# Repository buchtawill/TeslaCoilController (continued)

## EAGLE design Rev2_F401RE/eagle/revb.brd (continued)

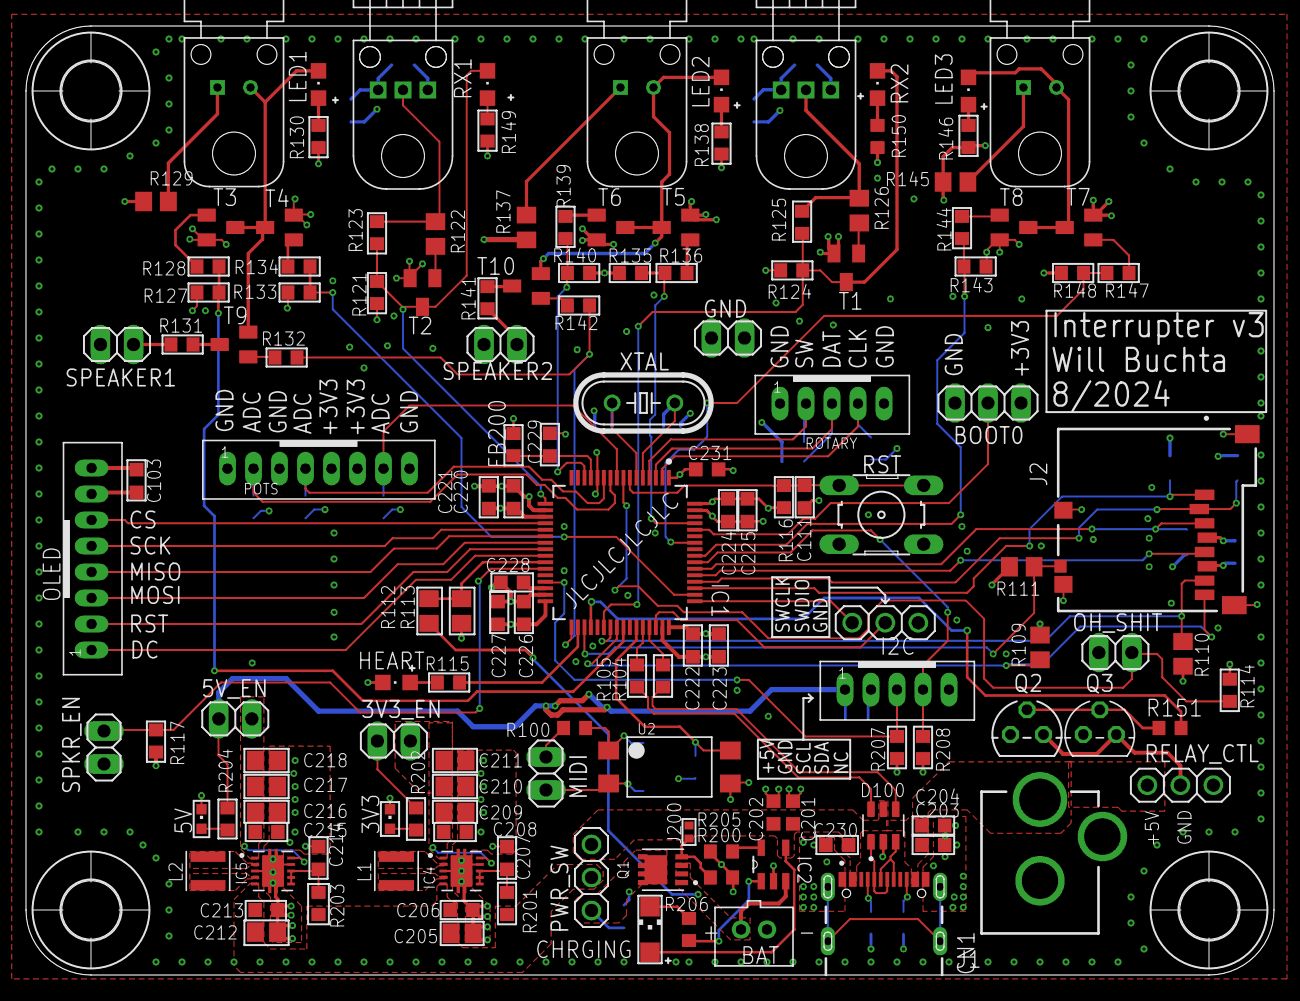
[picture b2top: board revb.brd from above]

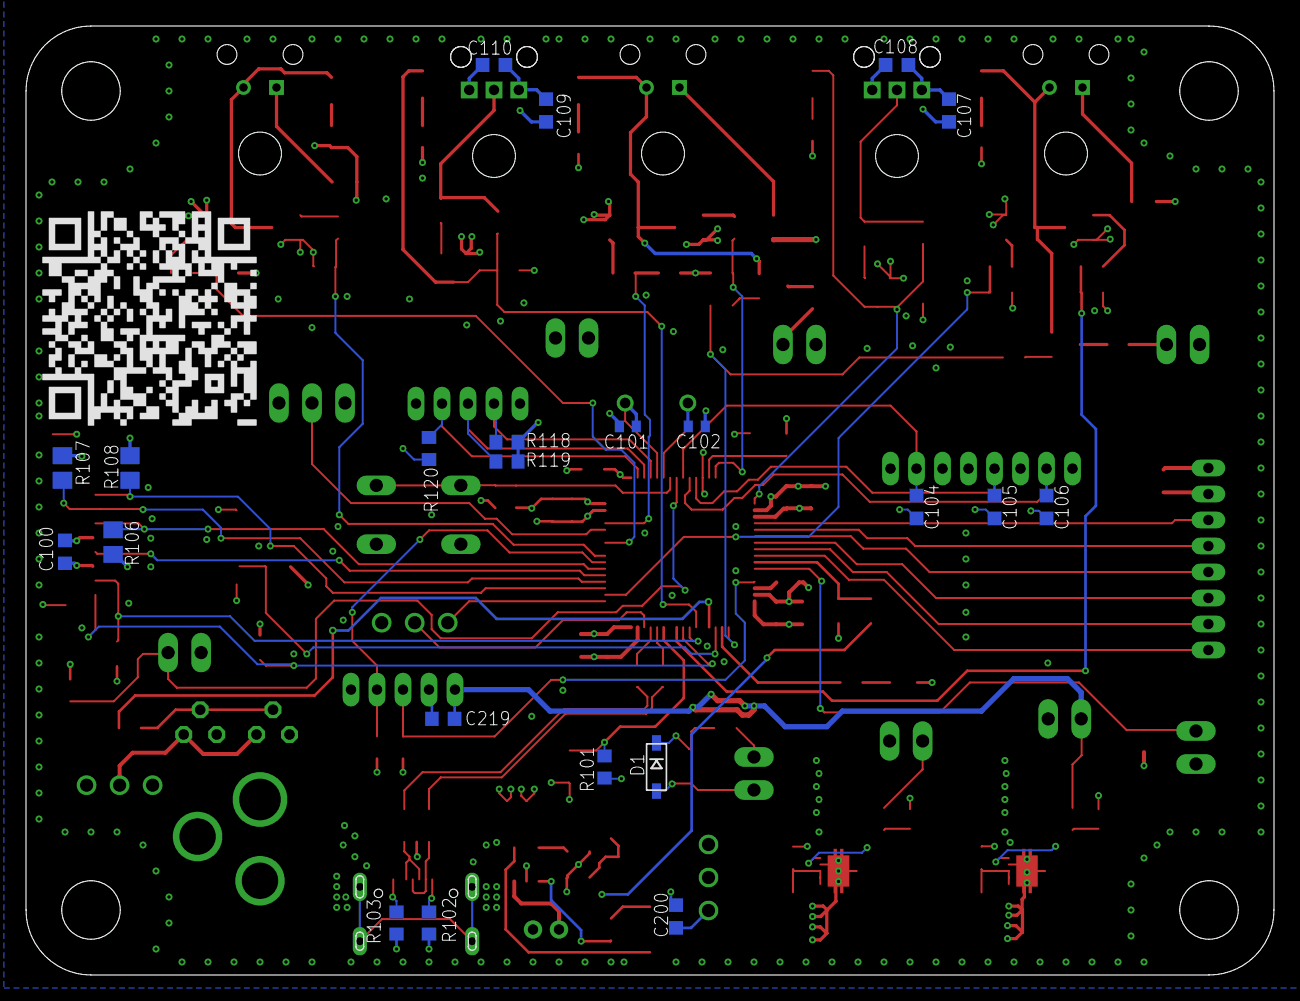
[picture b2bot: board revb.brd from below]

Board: 4 copper layers, 96.0 x 73.0 mm, 169 parts (22 on the bottom side), 107 nets.

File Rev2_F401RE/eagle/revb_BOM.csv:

Qty,Value,Device,Package,Parts,Description,Column1,_1
1,,10-XX,B3F-10XX,RST,OMRON SWITCH,,
1,,CRYSTALHC49S,HC49/S,XTAL,CRYSTAL,,
1,,JST_2PIN-THM,JST-PH-2-THM,BAT,JST 2-Pin Connectors of various flavors,,
2,,LEDCHIPLED_0603,CHIPLED_0603,"3V3, 5V",LED,,
6,,LEDCHIPLED_0805,CHIPLED_0805,"HEART, LED1, LED2, LED3, RX1, RX2",LED,,
1,,LEDCHIPLED_1206,CHIPLED_1206,CHRGING,LED,,
6,,PINHD-1X2,1X02,"GND, MIDI, OH_SHIT, SPEAKER1, SPEAKER2, SPKR_EN",PIN HEADER,,
3,,PINHD-1X3,1X03,"BOOT0, PWR_SW, SWD",PIN HEADER,,
1,0,R-US_R0402,R0402,J200,"RESISTOR, American symbol",,
2,0,R-US_R0603,R0603,"R123, R125","RESISTOR, American symbol",,
3,100,R-US_R0603,R0603,"FB200, R201, R203","RESISTOR, American symbol",,
3,100,R-US_R0805,R0805,"R129, R137, R145","RESISTOR, American symbol",,
21,100n,C-USC0603K,C0603K,"C100, C103, C108, C110, C200, C202, C203, C206, C207, C208, C213, C214, C215, C219, C220, C222, C224, C226, C229, C230, C231","CAPACITOR, American symbol",,
7,10k,R-US_R0805,R0805,"R106, R107, R108, R110, R111, R112, R113","RESISTOR, American symbol",,
1,10k\,R-US_R0805,R0805,R109,"RESISTOR, American symbol",,
3,10n,C-USC0603K,C0603K,"C105, C106, C111","CAPACITOR, American symbol",,
1,10n\,C-USC0603K,C0603K,C104,"CAPACITOR, American symbol",,
8,10u,C-USC0805,C0805,"C205, C209, C210, C211, C212, C216, C217, C218","CAPACITOR, American symbol",,
1,1k,R-US_R0603,R0603,R206,"RESISTOR, American symbol",,
2,1k,R-US_R0805,R0805,"R122, R126","RESISTOR, American symbol",,
9,1u,C-USC0603K,C0603K,"C107, C109, C201, C204, C221, C223, C225, C227, C228","CAPACITOR, American symbol",,
1,220,R-US_R0603,R0603,R100,"RESISTOR, American symbol",,
2,27,R-US_R0603,R0603,"R104, R105","RESISTOR, American symbol",,
2,27p,C-USC0402,C0402,"C101, C102","CAPACITOR, American symbol",,
14,2k2,R-US_R0603,R0603,"R115, R128, R130, R132, R134, R136, R138, R139, R142, R144, R146, R147, R149, R150","RESISTOR, American symbol",,
1,4148,DIODESOD-123,SOD-123,D1,Diode,,
2,470,R-US_R0603,R0603,"R131, R141","RESISTOR, American symbol",,
23,4k7,R-US_R0603,R0603,"R101, R102, R103, R114, R116, R117, R118, R119, R120, R121, R124, R127, R133, R135, R140, R143, R148, R200, R202\, R204\, R205, R207, R208","RESISTOR, American symbol",,
2,IF-D95,IF-D95,IFD95,"IF1, IF2",,,
3,IF-E95E,IF-E95E,IF-E96E,"TX1, TX2, TX3",,,
2,JST-PH_5-PIN_HEADER,JST-PH_5-PIN_HEADER,JST_B5B-PH_HEADER,"I2C, ROTARY","5-pin JST PH Shrouded Header, top entry",,
2,JST-PH_8-PIN_HEADER,JST-PH_8-PIN_HEADER,JST_B8B-PH_HEADER,"OLED, POTS",,,
2,LQH3NPN2R2MJRL,LQH3NPN2R2MJRL,IND_LQH3NPN2R2MJRL,"L1, L2",Inductor Power Chip Shielded Wirewound 33uH 20% 1MHz Ferrite 0.63A 0.948Ohm DCR 1212 T/R,,
1,LTV-816S,SMD-PHOTOCOUPLER-5KV-LTV-816S(4P-4.6X6.5MM),SMD4-2.54-4.6X6.5MM,U2,306060007,,
1,MCP73832,MCP73831T-2ACI/OT,SOT95P280X145-5N,IC2,Charge Management Controller,,
1,MEM2051-0019500A,MEM2051-00-195-00-A_REVD1MEM2051-00-195-00-A_GCT_MEM2051-00-195-00-A,GCT_MEM2051-00-195-00-A_REVD1,J2,,,
10,MMBTA06-7-F,BCV72SMD,SOT23-BEC,"T1, T2, T3, T4, T5, T6, T7, T8, T9, T10",NPN Transistor,,
4,MOUNT-HOLE4.5,MOUNT-HOLE4.5,"4,5","H1, H2, H3, H4",MOUNTING HOLE with drill center marker,,
1,SI7615,SI7611DN-T1-GE3,VISHAY_SIS468DN-T1-GE3,Q1,P-Channel 40 V 0.025 Ohm 39 W Surface Mount Power Mosfet - PowerPAK-1212-8 Check availability,,
1,STM32F401RE,STM32F401RET6,LQFP64-10X10MM,IC1,,,
1,TPS63001,TPS63001DRCR,VREG_V62/16624-01YE,IC4,,,
1,TPS63002,TPS63001DRCR,VREG_V62/16624-01YE,IC5,,,
1,USB4105-GF-A,USB4105-GF-A,GCT_USB4105-GF-A,J1,,,
1,USBLC6-2SC6,USBLC6-2SC6,SOT95P280X145-6N,D100,Check availability  Check availability,,

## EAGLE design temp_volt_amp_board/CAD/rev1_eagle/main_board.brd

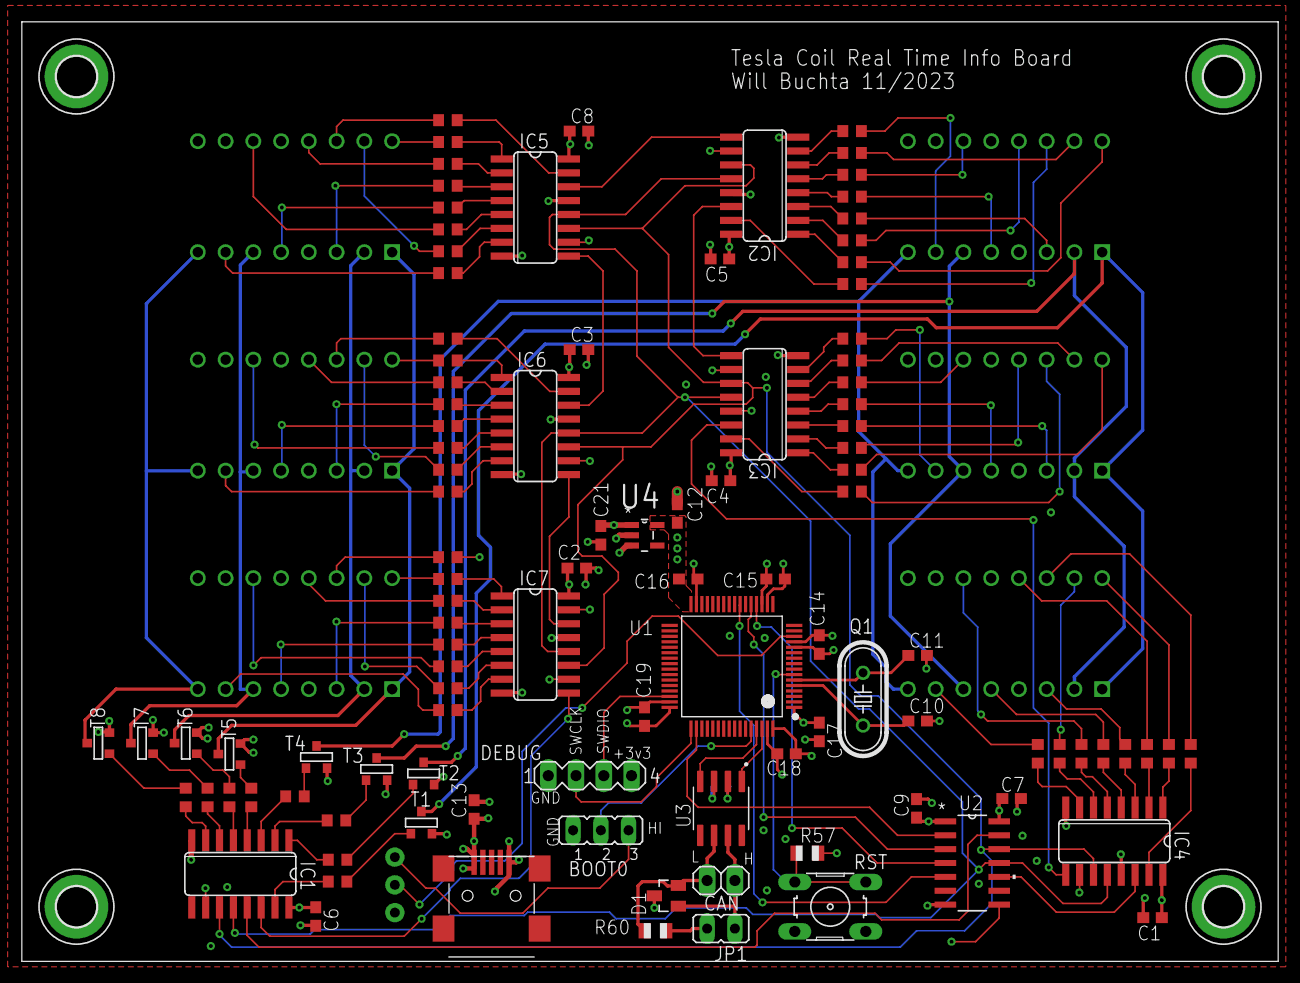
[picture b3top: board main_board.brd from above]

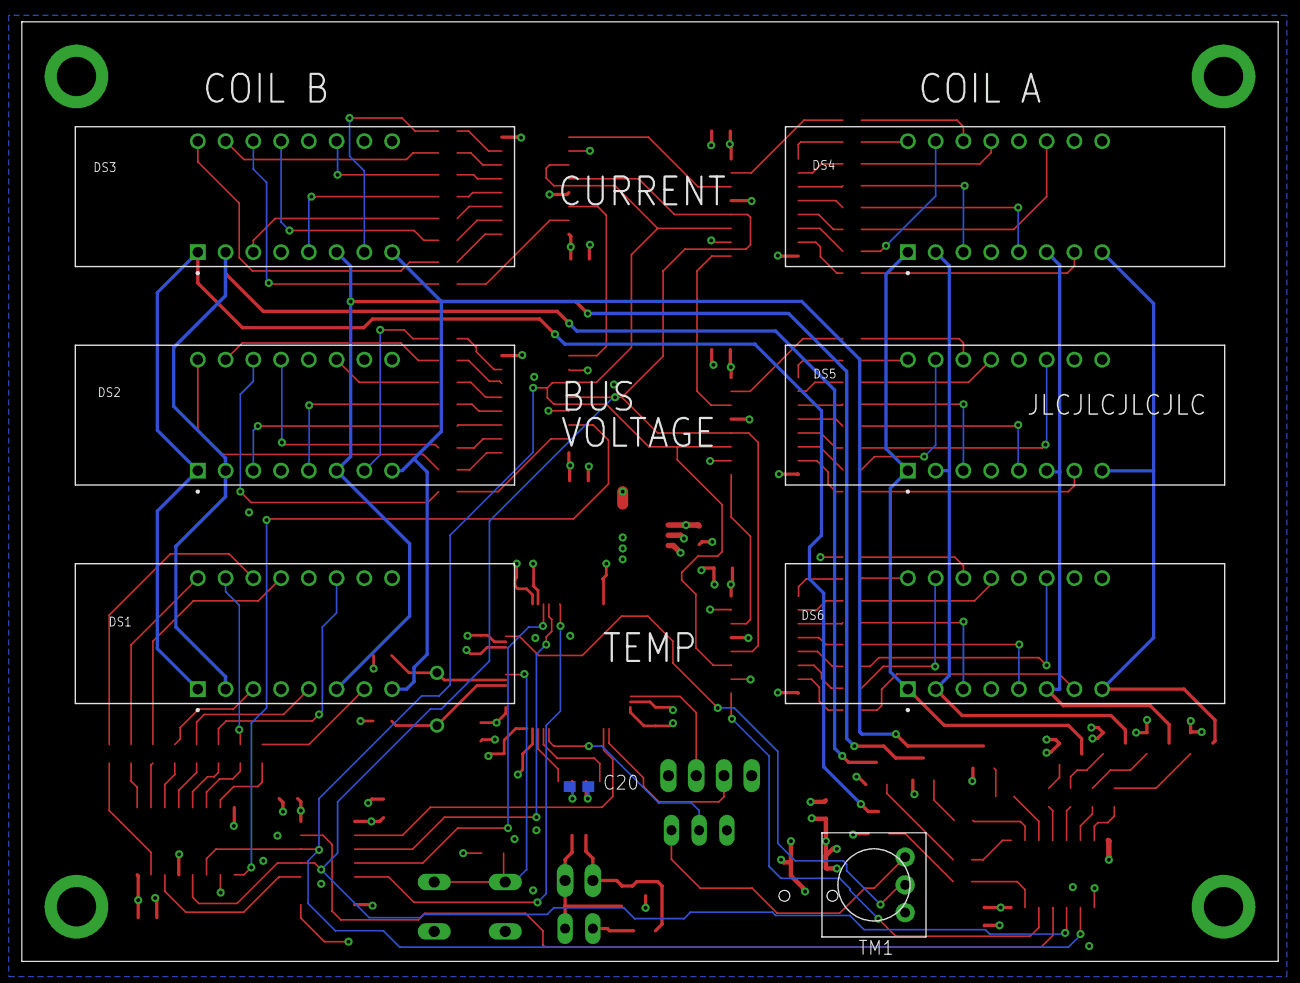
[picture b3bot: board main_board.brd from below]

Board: 4 copper layers, 115.0 x 86.0 mm, 117 parts (8 on the bottom side), 149 nets.

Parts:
BOOT0: JP2
C1, C2, C3, C4, C5, C6, C7, C8, C9, C13, C14, C15, C16, C17, C18, C19, C20: 100n; C0603
C10, C11: 30p; C0603
C12, C21: 1u; C0603
CAN: 1X02
CN1: USB-MINIB
D1: PESD1CAN; SOT23
DEBUG: MA04-1
DS1, DS2, DS3, DS4, DS5, DS6: TDCR1060M; DISPLAY_TDCR1060M
H1, H2, H3, H4: MOUNT-PAD-ROUND3.6; 3,6-PAD
IC1, IC2, IC3, IC4, IC5, IC6, IC7: 74LS595D; SO16
JP1: JP1
Q1: HC49/S
R1, R2, R3, R4, R5, R6, R7, R8, R9, R10, R11, R12, R13, R14, R15, R16, R17, R18, R19, R20, R21, R22, R23, R24, R25, R26, R27, R28, R29, R30, R31, R32, R33, R34, R35, R36, R37, R38, R39, R40, R41, R42, R43, R44, R45, R46, R47, R48, R49, R50, R51, R52, R53, R54, R55, R56: R0603
R57: 1k; R0805
R60: 120; R0805
RST: B3F-10XX
T1, T2, T3, T4, T5, T6, T7, T8: SOT-23
TM1: TRIM-3386
U1: STM32F105R8T6; QFP50P1200X1200X160-64N
U2: TXB0104DR; D14
U3: TCAN332DR; SOIC127P599X175-8N
U4: ADP122AUJZ-3.3-R7; SOT95P280X100-5N

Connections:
!OE: IC1.13, U2.13
+3V3: BOOT0.3, C9.1, C12.1, C14.1, C15.1, C16.1, C17.1, C18.1, C19.1, C20.1, DEBUG.4, R57.2, TM1.3, U1.1, U1.13, U1.19, U1.32, U1.48, U1.64, U2.1, U2.8, U3.3, U4.5
+5V: C1.1, C2.1, C3.1, C4.1, C5.1, C6.1, C7.1, C8.1, C13.1, C21.1, CN1.VBUS, IC1.10, IC1.16, IC2.10, IC2.16, IC3.10, IC3.16, IC4.10, IC4.16, IC5.10, IC5.16, IC6.10, IC6.16, IC7.10, IC7.16, U2.14, U4.1, U4.3
ADC1_IN0: TM1.2, U1.14
B1: R49.2, T1.3
B2: R50.2, T2.3
B3: R51.2, T3.3
B4: R52.2, T4.3
B5: R53.2, T5.3
B6: R54.2, T6.3
B7: R55.2, T7.3
B8: R56.2, T8.3
C1: DS1.8, DS2.8, DS3.8, T4.1
C2: DS1.6, DS2.6, DS3.6, T3.1
C3: DS1.2, DS2.2, DS3.2, T2.1
C4: DS1.1, DS2.1, DS3.1, T1.1
C5: DS4.8, DS5.8, DS6.8, T8.1
C6: DS4.6, DS5.6, DS6.6, T7.1
C7: DS4.2, DS5.2, DS6.2, T6.1
C8: DS4.1, DS5.1, DS6.1, T5.1
CAN_RX: U1.61, U3.4
CAN_TX: U1.62, U3.1
GND: BOOT0.1, C1.2, C2.2, C3.2, C4.2, C5.2, C6.2, C7.2, C8.2, C9.2, C10.2, C11.2, C12.2, C13.2, C14.2, C15.2, C16.2, C17.2, C18.2, C19.2, C20.2, C21.2, CN1.GND, D1.3, DEBUG.1, H1.B3,6, H2.B3,6, H3.B3,6, H4.B3,6, IC1.8, IC2.8, IC2.13, IC3.8, IC3.13, IC4.8, IC4.13, IC5.8, IC5.13, IC6.8, IC6.13, IC7.8, IC7.13, RST.3, RST.4, T1.2, T2.2, T3.2, T4.2, T5.2, T6.2, T7.2, T8.2, TM1.1, U1.12, U1.18, U1.31, U1.47, U1.63, U2.7, U3.2, U4.2
unnamed: IC2.15, R1.1
unnamed: IC2.1, R2.1
unnamed: IC2.2, R3.1
unnamed: IC2.3, R4.1
unnamed: IC2.4, R5.1
unnamed: IC2.5, R6.1
unnamed: IC2.6, R7.1
unnamed: IC2.7, R8.1
unnamed: IC3.15, R9.1
unnamed: IC3.1, R10.1
unnamed: IC3.2, R11.1
unnamed: IC3.3, R12.1
unnamed: IC3.4, R13.1
unnamed: IC3.5, R14.1
unnamed: IC3.6, R15.1
unnamed: IC3.7, R16.1
unnamed: DS2.7, R16.2
unnamed: DS2.15, R15.2
unnamed: DS2.11, R14.2
unnamed: DS2.5, R13.2
unnamed: DS2.3, R12.2
unnamed: DS2.13, R11.2
unnamed: DS2.16, R10.2
unnamed: DS2.14, R9.2
unnamed: DS3.7, R8.2
unnamed: DS3.15, R7.2
unnamed: DS3.11, R6.2
unnamed: DS3.5, R5.2
unnamed: DS3.3, R4.2
unnamed: DS3.13, R3.2
unnamed: DS3.16, R2.2
unnamed: DS3.14, R1.2
unnamed: IC4.15, R17.1
unnamed: IC4.1, R18.1
unnamed: IC4.2, R19.1
unnamed: IC4.3, R20.1
unnamed: IC4.4, R21.1
unnamed: IC4.5, R22.1
unnamed: IC4.6, R23.1
unnamed: IC4.7, R24.1
unnamed: DS1.7, R24.2
unnamed: DS1.15, R23.2
unnamed: DS1.11, R22.2
unnamed: DS1.5, R21.2
unnamed: DS1.3, R20.2
unnamed: DS1.13, R19.2
unnamed: DS1.16, R18.2
unnamed: DS1.14, R17.2
unnamed: IC5.15, R25.1
unnamed: IC5.1, R26.1
unnamed: IC5.2, R27.1
unnamed: IC5.3, R28.1
unnamed: IC5.4, R29.1
unnamed: IC5.5, R30.1
unnamed: IC5.6, R31.1
unnamed: IC5.7, R32.1
unnamed: DS4.7, R32.2
unnamed: DS4.15, R31.2
unnamed: DS4.11, R30.2
unnamed: DS4.5, R29.2
unnamed: DS4.3, R28.2
unnamed: DS4.13, R27.2
unnamed: DS4.16, R26.2
unnamed: DS4.14, R25.2
unnamed: IC6.15, R33.1
unnamed: IC6.1, R34.1
unnamed: IC6.2, R35.1
unnamed: IC6.3, R36.1
unnamed: IC6.4, R37.1
unnamed: IC6.5, R38.1
unnamed: IC6.6, R39.1
unnamed: IC6.7, R40.1
unnamed: DS5.7, R40.2
unnamed: DS5.15, R39.2
unnamed: DS5.11, R38.2
unnamed: DS5.5, R37.2
unnamed: DS5.3, R36.2
unnamed: DS5.13, R35.2
unnamed: DS5.16, R34.2
unnamed: DS5.14, R33.2
unnamed: IC7.15, R41.1
unnamed: IC7.1, R42.1
unnamed: IC7.2, R43.1
unnamed: IC7.3, R44.1
unnamed: IC7.4, R45.1
unnamed: IC7.5, R46.1
unnamed: IC7.6, R47.1
unnamed: IC7.7, R48.1
unnamed: DS6.7, R48.2
unnamed: DS6.15, R47.2
unnamed: DS6.11, R46.2
unnamed: DS6.5, R45.2
unnamed: DS6.3, R44.2
unnamed: DS6.13, R43.2
unnamed: DS6.16, R42.2
unnamed: DS6.14, R41.2
unnamed: IC2.9, IC5.14
unnamed: IC5.9, IC6.14
unnamed: IC6.9, IC7.14
unnamed: IC3.14, IC4.9
unnamed: IC2.14, IC3.9
unnamed: IC1.14, IC7.9
unnamed: CAN.1, D1.1, JP1.1, U3.7
unnamed: CAN.2, D1.2, R60.1, U3.6
unnamed: JP1.2, R60.2
unnamed: R57.1, RST.1, RST.2, U1.7
unnamed: C10.1, Q1.1, U1.5
unnamed: C11.1, Q1.2, U1.6
unnamed: BOOT0.2, U1.60
unnamed: IC1.15, R49.1
unnamed: IC1.1, R50.1
unnamed: IC1.2, R51.1
unnamed: IC1.3, R52.1
unnamed: IC1.4, R53.1
unnamed: IC1.5, R54.1
unnamed: IC1.6, R55.1
unnamed: IC1.7, R56.1
PWM: U1.50, U2.2
RCK: IC1.12, IC2.12, IC3.12, IC4.12, IC5.12, IC6.12, IC7.12, U2.11
RCK_STM: U1.20, U2.4
SCK: IC1.11, IC2.11, IC3.11, IC4.11, IC5.11, IC6.11, IC7.11, U2.12
SDI: IC4.14, U2.10
SPI_MOSI: U1.23, U2.5
SPI_SCK: U1.21, U2.3
SWCLK: DEBUG.2, U1.49
SWDIO: DEBUG.3, U1.46

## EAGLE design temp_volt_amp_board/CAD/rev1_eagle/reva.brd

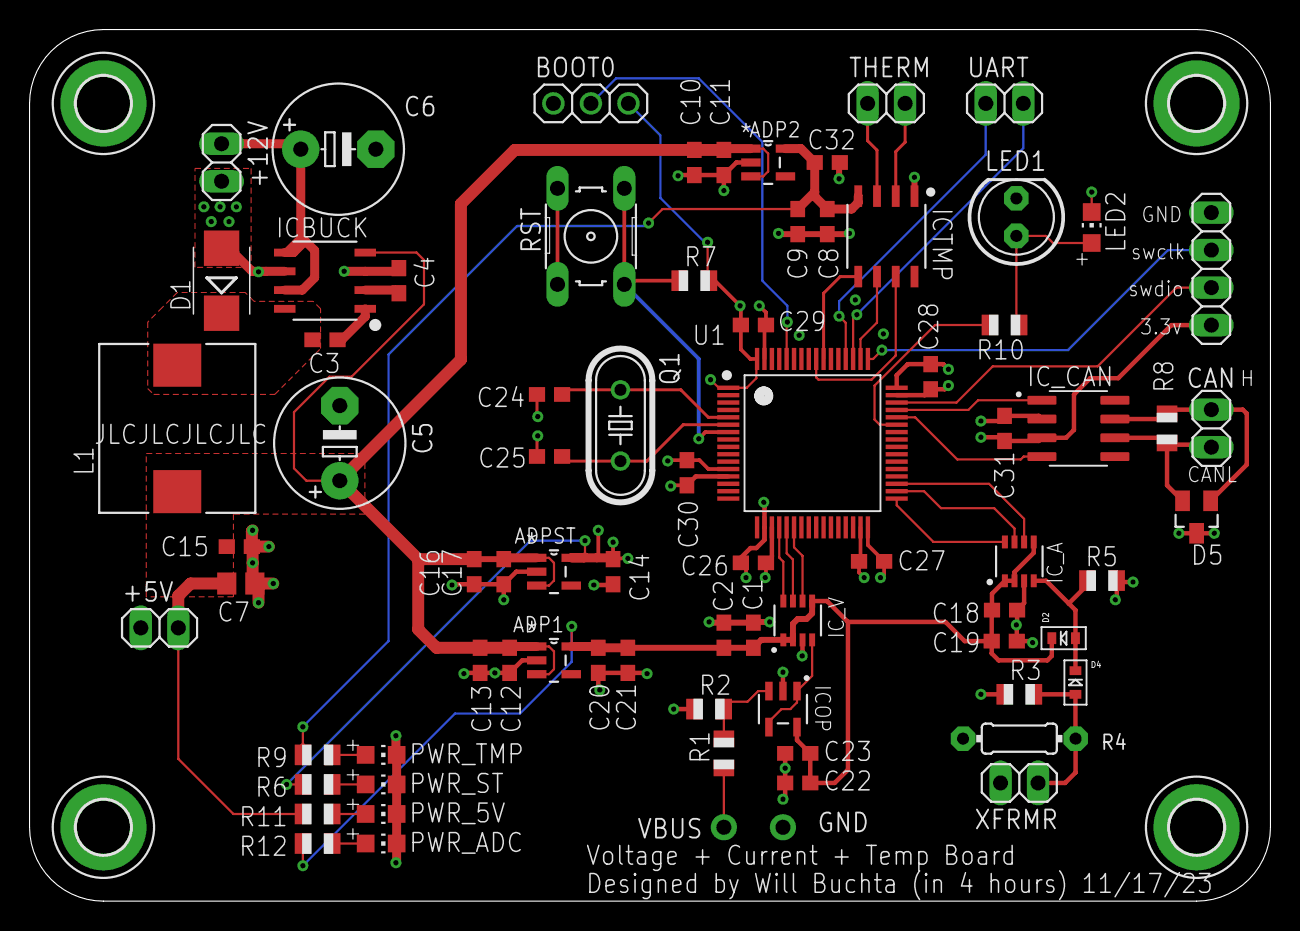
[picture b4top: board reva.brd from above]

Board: 4 copper layers, 84.0 x 59.0 mm, 81 parts (0 on the bottom side), 43 nets.

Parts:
+5V, +12V: 1X02
ADP1, ADP2: ADP122AUJZ-3.3-R7; SOT95P280X100-5N
ADPST: ADP122AUJZ-3.3-R7; SOT95P280X100-5N
BOOT0: 1X03
C1, C3, C4, C8, C11, C13, C17, C19, C21, C23, C24, C25, C26, C27, C28, C29, C30, C31: 100n; C0603
C2, C9, C10, C12, C14, C15, C16, C18, C20, C22, C32: 1u; C0603
C5, C6: 68u; E5-8,5
C7: 10u; C0805
CAN: 1X02
D1: SMB
D2, D4: SOD-523
D5: PESD1CAN; SOT23
GND: 1X01-CLEANBIG
H1, H2, H3, H4: MOUNT-PAD-ROUND3.6; 3,6-PAD
ICBUCK: MAX5035BUSA+T; 21-0041B_8_MXM
ICOP: AD8531; RJ_5_ADI
ICTMP: MAX31855KASA+T; 21-0041B_8_MXM
IC_A: LTC2365; TSOT-23_TS8_LIT
IC_CAN: TCAN332DR; SOIC127P599X175-8N
IC_V: LTC2365; TSOT-23_TS8_LIT
JP1: 1X04
L1: IHLP4040DZER101M11; IND_IHLP-4040DZ_VIS
LED1: LED5MM
LED2: CHIP-LED0805
PWR_5V: CHIP-LED0805
PWR_ADC: CHIP-LED0805
PWR_ST: CHIP-LED0805
PWR_TMP: CHIP-LED0805
Q1: HC49/S
R1: 900k; R0805
R2: 100k; R0805
R3: R0805
R4: 0204/7
R5, R7: 10k; R0805
R6, R9, R10, R11, R12: 1k; R0805
R8: 120; R0805
RST: B3F-10XX
THERM: 1X02
U1: STM32F105R8T6; QFP50P1200X1200X160-64N
UART: 1X02
VBUS: 1X01-CLEANBIG
XFRMR: 1X02

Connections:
+5V: +5V.2, ADP1.1, ADP1.3, ADP2.1, ADP2.3, ADPST.1, ADPST.3, C5.+, C7.1, C10.1, C11.1, C12.1, C13.1, C15.1, C16.1, C17.1, ICBUCK.4, L1.1, R11.2
+12V: +12V.2, C6.+, ICBUCK.5, ICBUCK.7
AINV: ICOP.1, ICOP.4, IC_V.4
CANH: CAN.2, D5.1, IC_CAN.7, R8.2
CANL: CAN.1, D5.2, IC_CAN.6, R8.1
CAN_RX: IC_CAN.4, U1.44
CAN_TX: IC_CAN.1, U1.45
CUR+: D4.A, R3.2, R4.2, XFRMR.2
GND: +5V.1, +12V.1, ADP1.2, ADP2.2, ADPST.2, BOOT0.1, C1.2, C2.2, C4.2, C5.-, C6.-, C7.2, C8.2, C9.2, C10.2, C11.2, C12.2, C13.2, C14.2, C15.2, C16.2, C17.2, C18.2, C19.2, C20.2, C21.2, C22.2, C23.2, C24.2, C25.2, C26.2, C27.2, C28.2, C29.2, C30.2, C31.2, C32.2, D1.A, D5.3, GND.1, H1.B3,6, H2.B3,6, H3.B3,6, H4.B3,6, ICBUCK.3, ICBUCK.6, ICOP.2, ICTMP.1, IC_A.3, IC_CAN.2, IC_V.3, JP1.4, LED1.K, LED2.C, PWR_5V.C, PWR_ADC.C, PWR_ST.C, PWR_TMP.C, R2.1, R3.1, R4.1, R5.1, RST.3, RST.4, U1.12, U1.18, U1.31, U1.47, U1.63, XFRMR.1
HV: R1.1, VBUS.1
MAXPWR: ADP2.5, C8.1, C9.1, C32.1, ICTMP.4, R9.2
unnamed: C3.2, D1.C, ICBUCK.8, L1.2
unnamed: C3.1, ICBUCK.1
unnamed: PWR_ST.A, R6.1
unnamed: C4.1, ICBUCK.2
unnamed: PWR_TMP.A, R9.1
unnamed: PWR_5V.A, R11.1
unnamed: PWR_ADC.A, R12.1
unnamed: R7.1, RST.1, RST.2, U1.7
unnamed: R10.2, U1.43
unnamed: LED1.A, LED2.A, R10.1
unnamed: BOOT0.2, U1.60
unnamed: C24.1, Q1.1, U1.5
unnamed: C25.1, Q1.2, U1.6
RECTIFIED: D2.A, D4.K, IC_A.4, R5.2
SPI1_MISO: IC_V.6, U1.22
SPI1_NSS: IC_V.8, U1.20
SPI1_SCK: IC_V.7, U1.21
SPI2_MISO: IC_A.6, U1.35
SPI2_NSS: IC_A.8, U1.33
SPI2_SCK: IC_A.7, U1.34
SPI3_MISO: ICTMP.7, U1.56
SPI3_NSS: ICTMP.6, U1.50
SPI3_SCK: ICTMP.5, U1.55
SWCLK: JP1.3, U1.49
SWDIO: JP1.2, U1.46
T+: ICTMP.3, THERM.1
T-: ICTMP.2, THERM.2
UART_RX: U1.52, UART.1
UART_TX: U1.51, UART.2
VBUSIN: ICOP.3, R1.2, R2.2
VDD_OP: ADP1.5, C1.1, C2.1, C18.1, C19.1, C20.1, C21.1, C22.1, C23.1, D2.K, ICOP.5, IC_A.1, IC_A.2, IC_A.5, IC_V.1, IC_V.2, IC_V.5, R12.2
VDD_STM32: ADPST.5, BOOT0.3, C14.1, C26.1, C27.1, C28.1, C29.1, C30.1, C31.1, IC_CAN.3, JP1.1, R6.2, R7.2, U1.1, U1.13, U1.19, U1.32, U1.48, U1.64

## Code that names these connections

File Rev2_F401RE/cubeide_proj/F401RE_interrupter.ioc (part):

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Mcu.Name=STM32F401R(D-E)Tx
Mcu.Package=LQFP64
Mcu.UserName=STM32F401RETx
PA0-WKUP.Signal=S_TIM5_CH1
PA10.GPIOParameters=GPIO_PuPd
PA10.GPIO_PuPd=GPIO_NOPULL
PA10.Mode=Asynchronous
PA10.Signal=USART1_RX
PA13.Mode=Serial_Wire
PA13.Signal=SYS_JTMS-SWDIO
PA14.Mode=Serial_Wire
PA14.Signal=SYS_JTCK-SWCLK
PA15.Signal=S_TIM2_CH1_ETR
PA2.Mode=Asynchronous
PA2.Signal=USART2_TX
PA3.Mode=Asynchronous
PA3.Signal=USART2_RX
PA4.GPIOParameters=GPIO_PuPd,GPIO_Label
PA4.GPIO_Label=OLED_CS
PA4.GPIO_PuPd=GPIO_PULLUP
PA4.Signal=GPIO_Output
PA5.Mode=Full_Duplex_Master
PA5.Signal=SPI1_SCK
PA6.Mode=Full_Duplex_Master
PA6.Signal=SPI1_MISO
PA7.Mode=Full_Duplex_Master
PA7.Signal=SPI1_MOSI
PA8.Signal=S_TIM1_CH1
PA9.Mode=Asynchronous
PA9.Signal=USART1_TX
PB0.Signal=ADCx_IN8
PB1.GPIOParameters=GPIO_Label,GPIO_ModeDefaultEXTI
PB1.GPIO_Label=SPKR_EN_BTN
PB1.GPIO_ModeDefaultEXTI=GPIO_MODE_IT_FALLING
PB1.Signal=GPXTI1
PB10.Mode=I2C
PB10.Signal=I2C2_SCL
PB12.GPIOParameters=GPIO_Label
PB12.GPIO_Label=SPKR_EN
PB12.Signal=GPIO_Output
PB13.GPIOParameters=GPIO_Label
PB13.GPIO_Label=LED_HEARTBEAT
PB13.Signal=GPIO_Output
PB14.GPIOParameters=GPIO_Label
PB14.GPIO_Label=SDIO_DETECT
PB14.Signal=GPIO_Input
PB15.GPIOParameters=GPIO_Label
PB15.GPIO_Label=RELAY
PB15.Signal=GPIO_Output
PB3.Mode=I2C
PB3.Signal=I2C2_SDA
PB8.Signal=S_TIM10_CH1
PC0.GPIOParameters=GPIO_Label,GPIO_ModeDefaultEXTI
PC0.GPIO_Label=OH_SHIT_BTN
PC0.GPIO_ModeDefaultEXTI=GPIO_MODE_IT_FALLING
PC0.Signal=GPXTI0
PC1.Signal=ADCx_IN11
PC10.Mode=SD_4_bits_Wide_bus
PC10.Signal=SDIO_D2
PC11.Mode=SD_4_bits_Wide_bus
PC11.Signal=SDIO_D3
PC12.Mode=SD_4_bits_Wide_bus
PC12.Signal=SDIO_CK
PC13-ANTI_TAMP.GPIOParameters=GPIO_Label,GPIO_ModeDefaultEXTI
PC13-ANTI_TAMP.GPIO_Label=ROT_CLK
PC13-ANTI_TAMP.GPIO_ModeDefaultEXTI=GPIO_MODE_IT_FALLING
PC13-ANTI_TAMP.Signal=GPXTI13
PC14-OSC32_IN.GPIOParameters=GPIO_Label
PC14-OSC32_IN.GPIO_Label=ROT_DAT
PC14-OSC32_IN.Signal=GPIO_Input
PC15-OSC32_OUT.GPIOParameters=GPIO_Label,GPIO_ModeDefaultEXTI
PC15-OSC32_OUT.GPIO_Label=ROT_SW
PC15-OSC32_OUT.GPIO_ModeDefaultEXTI=GPIO_MODE_IT_FALLING
PC15-OSC32_OUT.Signal=GPXTI15
PC2.Signal=ADCx_IN12
PC3.Signal=ADCx_IN13
PC4.GPIOParameters=GPIO_Label
PC4.GPIO_Label=OLED_RST
PC4.Signal=GPIO_Output
PC5.GPIOParameters=GPIO_Label
PC5.GPIO_Label=OLED_DC
PC5.Signal=GPIO_Output
PC6.Mode=Asynchronous
PC6.Signal=USART6_TX
PC7.Mode=Asynchronous
PC7.Signal=USART6_RX
PC8.Mode=SD_4_bits_Wide_bus
PC8.Signal=SDIO_D0
PC9.Mode=SD_4_bits_Wide_bus
PC9.Signal=SDIO_D1
PD2.Mode=SD_4_bits_Wide_bus
PD2.Signal=SDIO_CMD
PH0\ -\ OSC_IN.Mode=HSE-External-Oscillator
PH0\ -\ OSC_IN.Signal=RCC_OSC_IN
PH1\ -\ OSC_OUT.Mode=HSE-External-Oscillator
PH1\ -\ OSC_OUT.Signal=RCC_OSC_OUT
RCC.HSE_VALUE=16000000
RCC.SYSCLKFreq_VALUE=64000000
RCC.SYSCLKSource=RCC_SYSCLKSOURCE_PLLCLK
board=custom

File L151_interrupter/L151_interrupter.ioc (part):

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Mcu.Name=STM32L151C(6-8-B)Tx
Mcu.Package=LQFP48
Mcu.UserName=STM32L151CBTx
PA0-WKUP1.GPIOParameters=GPIO_Label
PA0-WKUP1.GPIO_Label=Pot1
PA0-WKUP1.Mode=IN0
PA0-WKUP1.Signal=ADC_IN0
PA1.Signal=S_TIM2_CH2
PA10.GPIOParameters=GPIO_Label
PA10.GPIO_Label=ROT_DAT
PA10.Signal=GPIO_Input
PA11.Mode=Device
PA11.Signal=USB_DM
PA12.Mode=Device
PA12.Signal=USB_DP
PA13.Mode=Serial_Wire
PA13.Signal=SYS_JTMS-SWDIO
PA14.Mode=Serial_Wire
PA14.Signal=SYS_JTCK-SWCLK
PA15.GPIOParameters=GPIO_Speed,GPIO_PuPd,GPIO_Label
PA15.GPIO_Label=SD_CS
PA15.GPIO_PuPd=GPIO_PULLUP
PA15.GPIO_Speed=GPIO_SPEED_FREQ_MEDIUM
PA15.Signal=GPIO_Output
PA2.GPIOParameters=GPIO_Label
PA2.GPIO_Label=Pot2
PA2.Mode=IN2
PA2.Signal=ADC_IN2
PA3.Signal=S_TIM9_CH2
PA4.GPIOParameters=GPIO_Label
PA4.GPIO_Label=stat595_SCK
PA4.Signal=GPIO_Output
PA5.Signal=S_TIM2_CH1_ETR
PA6.Signal=S_TIM3_CH1
PA8.GPIOParameters=GPIO_Label,GPIO_ModeDefaultEXTI
PA8.GPIO_Label=ROT_BUT
PA8.GPIO_ModeDefaultEXTI=GPIO_MODE_IT_FALLING
PA8.Signal=GPXTI8
PA9.GPIOParameters=GPIO_Label
PA9.GPIO_Label=ROT_CLK
PA9.Signal=GPXTI9
PB0.GPIOParameters=GPIO_Label
PB0.GPIO_Label=LED_Heartbeat
PB0.Signal=GPIO_Output
PB1.GPIOParameters=GPIO_Label
PB1.GPIO_Label=Flash_/wp
PB1.Signal=GPIO_Output
PB10.Mode=I2C
PB10.Signal=I2C2_SCL
PB11.Mode=I2C
PB11.Signal=I2C2_SDA
PB12.GPIOParameters=GPIO_Label
PB12.GPIO_Label=SPI2_SS
PB12.Signal=GPIO_Output
PB13.Mode=Full_Duplex_Master
PB13.Signal=SPI2_SCK
PB14.Mode=Full_Duplex_Master
PB14.Signal=SPI2_MISO
PB15.Mode=Full_Duplex_Master
PB15.Signal=SPI2_MOSI
PB2.GPIOParameters=GPIO_Label
PB2.GPIO_Label=Flash_/Hold
PB2.Signal=GPIO_Output
PB3.GPIOParameters=GPIO_PuPd
PB3.GPIO_PuPd=GPIO_PULLUP
PB3.Mode=Full_Duplex_Master
PB3.Signal=SPI1_SCK
PB4.GPIOParameters=GPIO_PuPd
PB4.GPIO_PuPd=GPIO_PULLUP
PB4.Mode=Full_Duplex_Master
PB4.Signal=SPI1_MISO
PB5.GPIOParameters=GPIO_PuPd
PB5.GPIO_PuPd=GPIO_PULLUP
PB5.Mode=Full_Duplex_Master
PB5.Signal=SPI1_MOSI
PB6.Signal=S_TIM4_CH1
PB7.Signal=S_TIM4_CH2
PB8.Signal=S_TIM10_CH1
PB9.Signal=S_TIM11_CH1
PC13-WKUP2.GPIOParameters=GPIO_Label
PC13-WKUP2.GPIO_Label=stat595_SER
PC13-WKUP2.Signal=GPIO_Output
PH0-OSC_IN.Mode=HSE-External-Oscillator
PH0-OSC_IN.Signal=RCC_OSC_IN
PH1-OSC_OUT.Mode=HSE-External-Oscillator
PH1-OSC_OUT.Signal=RCC_OSC_OUT
RCC.HSE_VALUE=24000000
RCC.SYSCLKFreq_VALUE=32000000
RCC.SYSCLKSource=RCC_SYSCLKSOURCE_PLLCLK
board=custom

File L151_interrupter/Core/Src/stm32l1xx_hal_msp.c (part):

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
    __HAL_RCC_GPIOA_CLK_ENABLE();
    /**ADC GPIO Configuration
    PA0-WKUP1     ------> ADC_IN0
    PA2     ------> ADC_IN2
    */
    GPIO_InitStruct.Pin = Pot1_Pin|Pot2_Pin;
    GPIO_InitStruct.Mode = GPIO_MODE_ANALOG;
    GPIO_InitStruct.Pull = GPIO_NOPULL;
    HAL_GPIO_Init(GPIOA, &GPIO_InitStruct);
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    __HAL_RCC_ADC1_CLK_DISABLE();

    /**ADC GPIO Configuration
    PA0-WKUP1     ------> ADC_IN0
    PA2     ------> ADC_IN2
    */
    HAL_GPIO_DeInit(GPIOA, Pot1_Pin|Pot2_Pin);

    /* ADC1 DMA DeInit */
    HAL_DMA_DeInit(hadc->DMA_Handle);
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
    __HAL_RCC_GPIOB_CLK_ENABLE();
    /**I2C2 GPIO Configuration
    PB10     ------> I2C2_SCL
    PB11     ------> I2C2_SDA
    */
    GPIO_InitStruct.Pin = GPIO_PIN_10|GPIO_PIN_11;
    GPIO_InitStruct.Mode = GPIO_MODE_AF_OD;
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    __HAL_RCC_I2C2_CLK_DISABLE();

    /**I2C2 GPIO Configuration
    PB10     ------> I2C2_SCL
    PB11     ------> I2C2_SDA
    */
    HAL_GPIO_DeInit(GPIOB, GPIO_PIN_10);

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
    __HAL_RCC_GPIOB_CLK_ENABLE();
    /**SPI1 GPIO Configuration
    PB3     ------> SPI1_SCK
    PB4     ------> SPI1_MISO
    PB5     ------> SPI1_MOSI
    */
    GPIO_InitStruct.Pin = GPIO_PIN_3|GPIO_PIN_4|GPIO_PIN_5;
    GPIO_InitStruct.Mode = GPIO_MODE_AF_PP;
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
    __HAL_RCC_GPIOB_CLK_ENABLE();
    /**SPI2 GPIO Configuration
    PB13     ------> SPI2_SCK
    PB14     ------> SPI2_MISO
    PB15     ------> SPI2_MOSI
    */
    GPIO_InitStruct.Pin = GPIO_PIN_13|GPIO_PIN_14|GPIO_PIN_15;
    GPIO_InitStruct.Mode = GPIO_MODE_AF_PP;
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    __HAL_RCC_SPI1_CLK_DISABLE();

    /**SPI1 GPIO Configuration
    PB3     ------> SPI1_SCK
    PB4     ------> SPI1_MISO
    PB5     ------> SPI1_MOSI
    */
    HAL_GPIO_DeInit(GPIOB, GPIO_PIN_3|GPIO_PIN_4|GPIO_PIN_5);

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    __HAL_RCC_SPI2_CLK_DISABLE();

    /**SPI2 GPIO Configuration
    PB13     ------> SPI2_SCK
    PB14     ------> SPI2_MISO
    PB15     ------> SPI2_MOSI
    */
    HAL_GPIO_DeInit(GPIOB, GPIO_PIN_13|GPIO_PIN_14|GPIO_PIN_15);

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  /* USER CODE END TIM2_MspPostInit 0 */
    __HAL_RCC_GPIOA_CLK_ENABLE();
    /**TIM2 GPIO Configuration
    PA1     ------> TIM2_CH2
    PA5     ------> TIM2_CH1
    */
    GPIO_InitStruct.Pin = GPIO_PIN_1|GPIO_PIN_5;
    GPIO_InitStruct.Mode = GPIO_MODE_AF_PP;
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
    __HAL_RCC_GPIOA_CLK_ENABLE();
    /**TIM3 GPIO Configuration
    PA6     ------> TIM3_CH1
    */
    GPIO_InitStruct.Pin = GPIO_PIN_6;
    GPIO_InitStruct.Mode = GPIO_MODE_AF_PP;
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
    __HAL_RCC_GPIOB_CLK_ENABLE();
    /**TIM4 GPIO Configuration
    PB6     ------> TIM4_CH1
    PB7     ------> TIM4_CH2
    */
    GPIO_InitStruct.Pin = GPIO_PIN_6|GPIO_PIN_7;
    GPIO_InitStruct.Mode = GPIO_MODE_AF_PP;
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
    __HAL_RCC_GPIOA_CLK_ENABLE();
    /**TIM9 GPIO Configuration
    PA3     ------> TIM9_CH2
    */
    GPIO_InitStruct.Pin = GPIO_PIN_3;
    GPIO_InitStruct.Mode = GPIO_MODE_AF_PP;
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
    __HAL_RCC_GPIOB_CLK_ENABLE();
    /**TIM10 GPIO Configuration
    PB8     ------> TIM10_CH1
    */
    GPIO_InitStruct.Pin = GPIO_PIN_8;
    GPIO_InitStruct.Mode = GPIO_MODE_AF_PP;
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
    __HAL_RCC_GPIOB_CLK_ENABLE();
    /**TIM11 GPIO Configuration
    PB9     ------> TIM11_CH1
    */
    GPIO_InitStruct.Pin = GPIO_PIN_9;
    GPIO_InitStruct.Mode = GPIO_MODE_AF_PP;
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
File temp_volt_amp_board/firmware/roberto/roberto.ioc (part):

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Mcu.Name=STM32F105R(8-B-C)Tx
Mcu.Package=LQFP64
Mcu.UserName=STM32F105R8Tx
PA10.Signal=GPIO_Output
PA11.Mode=CAN_Activate
PA11.Signal=CAN1_RX
PA12.Mode=CAN_Activate
PA12.Signal=CAN1_TX
PA13.Mode=Serial_Wire
PA13.Signal=SYS_JTMS-SWDIO
PA14.Mode=Serial_Wire
PA14.Signal=SYS_JTCK-SWCLK
PA15.Mode=NSS_Signal_Hard_Output
PA15.Signal=SPI3_NSS
PA4.Mode=NSS_Signal_Hard_Output
PA4.Signal=SPI1_NSS
PA5.Mode=Full_Duplex_Master
PA5.Signal=SPI1_SCK
PA6.Mode=Full_Duplex_Master
PA6.Signal=SPI1_MISO
PA7.Mode=Full_Duplex_Master
PA7.Signal=SPI1_MOSI
PB12.Signal=SPI2_NSS
PB13.Mode=Full_Duplex_Master
PB13.Signal=SPI2_SCK
PB14.Mode=Full_Duplex_Master
PB14.Signal=SPI2_MISO
PB15.Mode=Full_Duplex_Master
PB15.Signal=SPI2_MOSI
PB3.Mode=Full_Duplex_Master
PB3.Signal=SPI3_SCK
PB4.Mode=Full_Duplex_Master
PB4.Signal=SPI3_MISO
PB5.Mode=Full_Duplex_Master
PB5.Signal=SPI3_MOSI
PC10.Mode=Asynchronous
PC10.Signal=UART4_TX
PC11.Mode=Asynchronous
PC11.Signal=UART4_RX
PD0-OSC_IN.Mode=HSE-External-Oscillator
PD0-OSC_IN.Signal=RCC_OSC_IN
PD1-OSC_OUT.Mode=HSE-External-Oscillator
PD1-OSC_OUT.Signal=RCC_OSC_OUT
RCC.SYSCLKFreq_VALUE=64000000
RCC.SYSCLKSource=RCC_SYSCLKSOURCE_PLLCLK
board=custom

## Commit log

2023-10-20 Import from local code
2023-10-20 Update README (and learn how to use git)
2023-10-20 Add mode description in README
2023-10-20 Change scroll to non-blocking delay
2023-10-20 Increase frequency limit
2023-10-21 Fix bugs and pray
2023-10-21 Implement cursor blinking functionality
2023-10-21 Fix burst mode
2023-10-21 Make Timers.c faster
2023-10-22 Backtrack I messed up
2023-10-22 Make sd mode faster
2023-10-22 Fix bugs and increase efficiency
2023-10-22 Add gitignore
2023-10-22 Update binaries
2023-10-22 Fix scroll on SD Mode
2023-10-22 Stop tracking binaries + debug files
2023-10-24 Bug fixes
2024-07-23 Add license to readme
2024-07-26 Initial commit for L433 interrupter
2024-07-26 Add L151 board files
2024-07-26 Move to separate folder, update ioc
2024-08-04 Create F401RE Project
2024-08-04 Create gitignore
2024-08-04 Modify ioc
2024-08-04 Ignore Debug
2024-08-04 Remove L433 interrupter (Use F401RE)
2024-08-04 Initial code generation and vscode setup
2024-08-05 Remove code workspace
2024-08-05 Initial upload
2024-08-05 Change clock freq to 16MHz
2024-08-10 Add Eagle files
2024-08-10 Finalize IO
2024-08-10 Remove Vsrc pin
2024-08-11 Add interrupts
2024-08-11 General updates
2024-08-13 Update documentation
2024-08-13 Remove unused include
2024-08-13 Update macros
2024-08-13 Incremental repo backkup
2024-08-14 Fix build
2024-08-14 Convert to CPP
2024-08-20 Reformat
2024-10-13 hindsight
2024-10-13 Print ontime twice
2024-10-13 Enable ADC CH2
2024-10-14 Ignore release build
2024-10-14 Create BOM
2024-10-14 Add DMA
2024-10-14 DMA only started in while loop
2024-10-14 ***WORKING*** Implement two channel ADC capture with DMA, coordinate channel volume
2024-10-15 Enable f_chdir function
2024-10-15 Implement directory capabilities
2024-10-15 Consolidate midi files to here
2024-10-15 Document bugs
2024-10-22 Update midi files
2024-10-25 Finish first bringup task: display on all LEDs
2024-10-25 Create basic application to demonstrate 7seg functionality
2024-10-26 Initial commit and code generation
2024-10-26 working Thermo Couple code. Tested in debugger. Not calibrated to a specific temperature source but temperature trend is consistent with external variables
2024-10-27 not working ADC code. Used for debugging at the moment. ONLY tested on SPI1 on yellow blue board.
2024-10-29 Fix MIDI
2024-10-29 Refactor
2024-10-29 Create base softuart functions
2024-10-30 Make prototype of application. Bug: Left display does not work
2024-10-30 Init commit
2024-10-30 Change systick to tim3
2024-10-30 Fix ontime nerfing
2024-10-30 Update MIDI
2024-10-30 Add message counter
2024-10-30 Updated midi
2024-10-31 Move modified file
2024-10-31 Finish modifying song
2024-10-31 Partial fix
2025-02-23 Add songs
2025-02-24 Modify FW
2025-02-24 Add barrel jack, add headers, add jumper between buck and rail, fix OLED pinout
2025-02-24 Save case state
2025-02-25 Add IO for a relay board
2025-02-25 Submit to JLC for assembly
2025-03-03 Add oneTesla interrupter FW
2025-04-04 Create new board for interactive case
2025-08-04 Sync workspace
2025-08-04 Remove auto-generated files
2025-08-04 Remove USB drivers
2025-08-04 Sync workspace [final]
2025-08-08 Implement UART receive and timer programming
2025-08-08 Stop PWM glitches at boot
2025-08-14 Update timers to force-update timer after programming
2025-08-15 Implement basic state machine for LCD and interrupter state
2025-08-16 Move main and menu to C++, implement pitch bend, add extern c guards
2025-08-26 Created lcd-menu branch
2025-08-26 Test signing
2025-09-17 Started adding templates for menu classes
2025-09-17 Added Tim9; TODO: Need to figure out why it is activating at 1428 ms instead of 1000 ms
2025-09-17 Sync changes
2025-10-26 Sync work
2025-10-26 Clean up code
2025-10-27 Create wave files for each output
2025-10-27 Add spooky song
2025-10-28 Remove duplicate notes
2025-11-18 Move to EDA folder
2025-11-18 Change back to C
2025-12-04 New STM32F105R8 Rev
2025-12-05 Add ADC support
